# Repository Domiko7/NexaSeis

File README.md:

<p align="center">
  An open-source, collaborative seismic monitoring network built around affordable ESP32-based stations.
</p>

> [!WARNING]
> **NexaSeis is incomplete and under active development.** Expect unfinished features, breaking changes, and limited documentation. Do not rely on it for safety-critical earthquake monitoring or emergency alerts. Of the projects in `seismometer/`, only **NX-1D** is currently complete; NX-LSM6DS3 and NX-ADXL355 remain unfinished.

## Overview

NexaSeis collects waveform samples from networked seismometers, processes and stores them, and makes live station data available to other applications. This repository contains the complete stack:

- a Python ingestion and processing server;
- a Vue web interface for viewing the network and individual stations;
- firmware and KiCad design files for several ESP32-based seismometers;
- optional WebSocket, DataLink, SeedLink, and REST API services.

The server can be installed as a Python package, while its runtime behavior and station inventory remain controlled by a JSON configuration file.

## How it works

```text
ESP32 station ──UDP/TCP──> Python server ──> signal processing ──> SQLite
                                │
                                ├──> REST API / helicorders
                                ├──> WebSocket stream
                                ├──> DataLink
                                └──> SeedLink
```

Stations send fixed-size binary packets containing a timestamp, station identifiers, and five signed integer samples. The server matches each packet to a station in `src/config.json`, applies its channel sensitivity and sample rate, buffers the waveform, calculates ground-motion values, and dispatches the result to enabled outputs.

## Repository layout

| Path | Purpose |
| --- | --- |
| `src/nexaseis/` | Python server, processing pipeline, database, and services |
| `src/config.json` | Server, station, and output configuration |
| `nexaseis-web/` | Vue 3, Vuetify, and Vite web application |
| `seismometer/NX-1D/` | Complete ESP32 firmware for the ADS1256-based one-axis station |
| `seismometer/NX-LSM6DS3/` | Unfinished ESP32 firmware and KiCad hardware files for LSM6DS3 stations |
| `seismometer/NX-ADXL355/` | Unfinished ESP32/ADXL355 firmware project |
| `fdsnws/stations/` | FDSN StationXML metadata |
| `scripts/` | Development and integration helper scripts |

See the [seismometer guide](seismometer/README.md) for hardware status, NX-1D setup, and important filter limitations.

For a practical overview of the hardware, read [How to build a DIY seismometer](https://domiko.dev/blog/diy-seismometer).

## Requirements

### Server

- Python 3.11 or newer
- `obspy`
- `websockets`
- `simpledali`
- `simplemseed`
- `uvicorn`
- `fastapi[standard]`
- `numpy`

SQLite support is provided by Python's standard library and does not need a separate package.

### Web application

- Node.js 20.19+ or 22.12+
- npm

### Firmware

- PlatformIO
- an ESP32 development board
- the sensor and electronics appropriate for the selected hardware variant

## Server setup

1. Create and activate a virtual environment:

   ```bash
   python3 -m venv .venv
   source .venv/bin/activate
   ```

2. Install NexaSeis and its runtime dependencies in editable mode:

   ```bash
   python -m pip install --upgrade pip
   python -m pip install -e .
   ```

3. Edit `src/config.json`. At minimum, change `data_path` to an absolute directory writable by the server process and configure the station records you intend to receive.

4. Start the server from the repository root:

   ```bash
   ./run.sh
   ```

   The installed command and equivalent module command are:

   ```bash
   nexaseis
   python -m nexaseis
   ```

By default, a source checkout reads `src/config.json`. To keep configuration elsewhere, set `NEXASEIS_CONFIG` to its path before starting the server:

```bash
export NEXASEIS_CONFIG=/absolute/path/to/config.json
nexaseis
```

With the checked-in example configuration, the server listens on:

| Service | Default address | Purpose |
| --- | --- | --- |
| UDP ingest | `0.0.0.0:50006` | Receives station packets |
| REST API | `0.0.0.0:50010` | Station state and helicorder images |
| WebSocket | `0.0.0.0:50007` | Streams processed packets |
| DataLink | `127.0.0.1:16000` | Forwards waveform data to a DataLink server |
| TCP ingest | `0.0.0.0:50005` | Optional TCP packet input; disabled by default |
| SeedLink | `0.0.0.0:18000` | Optional SeedLink service; disabled by default |

Binding to `0.0.0.0` exposes a service on every network interface. Use a firewall and more restrictive bind addresses where appropriate.

### Station configuration

Each entry in the `stations` array identifies a station by its network, code, and location. Channels define their own calibration and sampling parameters:

```json
{
  "name": "Example Station",
  "network": "XX",
  "code": "TEST",
  "location": "00",
  "channels": {
    "EHZ": {
      "sensitivity": 5408390926,
      "sample_rate": 100
    }
  },
  "lat": 52.0,
  "lon": 21.0,
  "elevation": 100
}
```

The network, station, location, and channel values sent by the device must match this configuration. Restart the server after changing the file; configuration is loaded at startup.

### API

When the API is enabled, interactive OpenAPI documentation is available at `http://localhost:50010/docs`.

Useful endpoints include:

- `GET /` — health and server time;
- `GET /stations` — latest processed values, grouped by station;
- `GET /helicorder/{network}/{code}/{location}/{channel}?type=standard` — generated helicorder image. `type` may be `standard`, `teleseismic`, or `raw`.

Waveform packets are persisted to `nexaseis.db` beneath the configured `data_path`.

## Web application

Run the development server:

```bash
cd nexaseis-web
npm ci
npm run dev
```

Create a production build:

```bash
npm run build
```

The compiled application is written to `nexaseis-web/dist/`. Preview it locally with `npm run preview`.

## Firmware

Only `seismometer/NX-1D/` is currently considered complete. The NX-LSM6DS3 and NX-ADXL355 directories contain unfinished development work and should not be expected to build or function correctly.

Read [`seismometer/README.md`](seismometer/README.md) before configuring the firmware. It documents the required NX-1D settings and the sensor-specific limitations of its compensation and high-pass filters.

Open the NX-1D directory as a PlatformIO project. Before uploading, review its `include/settings.h` and source files for Wi-Fi credentials, station identifiers, server address, sensor pins, and calibration values.

Build the NX-1D firmware from the command line:

```bash
cd seismometer/NX-1D
pio run
```

Connect the target ESP32 and upload with:

```bash
pio run --target upload
pio device monitor
```

Never commit real Wi-Fi credentials or other secrets. Keep local values in ignored files or inject them through PlatformIO build settings.

## Development checks

The web application provides the currently configured automated checks:

```bash
cd nexaseis-web
npm run lint
npm run build
```

There is not yet an automated Python or firmware test suite. When changing the server, verify startup with a writable `data_path` and exercise the relevant input/output service.

## License

NexaSeis is licensed under the [GNU Affero General Public License v3.0](LICENSE).

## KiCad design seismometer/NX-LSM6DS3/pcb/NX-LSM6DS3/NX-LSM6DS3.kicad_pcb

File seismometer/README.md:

# NexaSeis seismometers

This directory contains the firmware and hardware work for the NexaSeis sensing devices.

See [How to build a DIY seismometer](https://domiko.dev/blog/diy-seismometer) for the accompanying hardware build guide.

> [!WARNING]
> Only **NX-1D** is currently complete. **NX-LSM6DS3** and **NX-ADXL355** are unfinished development projects and should not be expected to build or operate correctly.

## Project status

| Project | Status | Description |
| --- | --- | --- |
| [`NX-1D`](NX-1D/) | Complete | ESP32 and ADS1256 firmware for a one-axis station |
| [`NX-LSM6DS3`](NX-LSM6DS3/) | Untested | Experimental LSM6DS3 firmware (104sps not 100sps!!) |
| [`NX-ADXL355`](NX-ADXL355/) | Incomplete | Early ADXL355 firmware project |

## NX-1D setup

NX-1D is a PlatformIO project targeting an ESP32 development board. Before building or uploading it, edit [`NX-1D/include/settings.h`](NX-1D/include/settings.h) for your station and hardware.

Review at least the following settings:

- `WIFI_SSID` and `WIFI_PASSWORD` — Wi-Fi credentials;
- `CODE`, `NETWORK`, `CHANNEL`, and `LOCATION` — seismic channel identifiers, which must match the server configuration;
- `SERVER_IP`, `SERVER_PORT`, and `TRANSMISSION_PROTOCOL` — NexaSeis server connection;
- `SAMPLE_RATE`, ADC gain, input pins, and ADS1256 register values;
- ESP32 SPI, data-ready, reset, and synchronization pins;
- `ENABLE_COMPENSATION` and `ENABLE_HIGH_PASS` — optional real-time filters described below.

Do not commit real credentials or private server details to the repository.

Build and upload from the NX-1D directory:

```bash
cd seismometer/NX-1D
pio run
pio run --target upload
pio device monitor
```

## Filter limitations

The implementations controlled by `ENABLE_COMPENSATION` and `ENABLE_HIGH_PASS` are designed **only for a 4.5 Hz geophone sampled at 100 samples per second**. Do not enable them for another sensor or sample rate without calculating and validating suitable filter coefficients.

Set both options explicitly in `NX-1D/include/settings.h`:

```cpp
#define ENABLE_COMPENSATION true
#define ENABLE_HIGH_PASS true
```

Set an option to `false` when its filter is not appropriate for the connected sensor or sampling configuration.

### A note on waveform distortion

While this filter allows a $35–$50 geophone to detect low-frequency teleseismic activity, real-time Infinite Impulse Response (IIR) filters introduce phase distortion. Because different frequencies experience slight differences in group delay, wave arrivals (like P-waves and S-waves) may appear visually smoothed or stretched. For real-time event detection on low-cost hardware, this trade-off is usually well worth it.

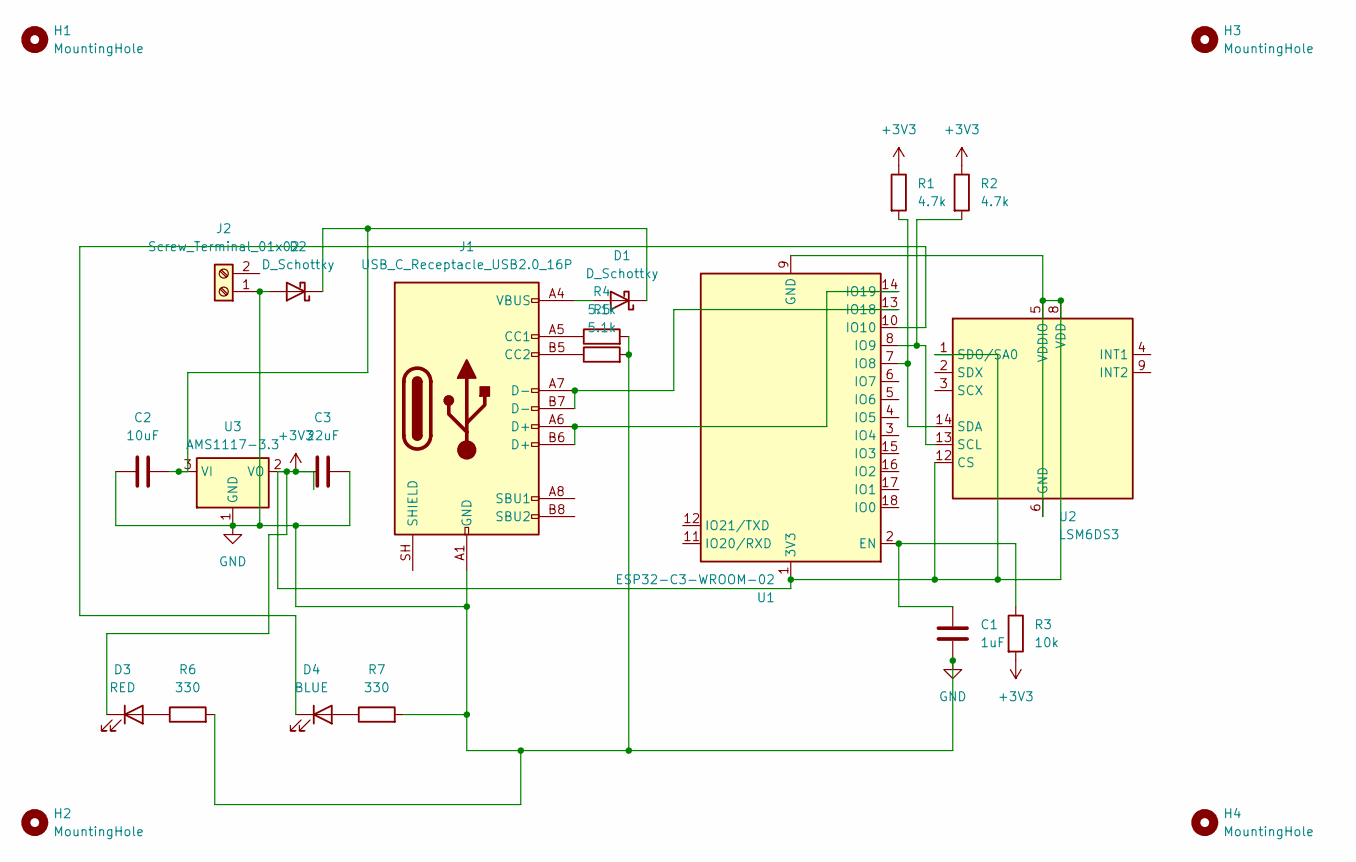
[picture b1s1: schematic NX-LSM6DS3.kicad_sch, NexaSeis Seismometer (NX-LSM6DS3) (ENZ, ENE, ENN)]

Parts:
C1: 1uF; C_0805_2012Metric
C2: 10uF; C_0805_2012Metric
C3: 22uF; C_0805_2012Metric
D1, D2: D_Schottky; D_SOD-123
D3: RED; LED_0805_2012Metric
D4: BLUE; LED_0805_2012Metric
H1, H2, H3, H4: MountingHole; MountingHole_3.2mm_M3_Pad
J1: USB_C_Receptacle_USB2.0_16P; USB_C_Receptacle_HRO_TYPE-C-31-M-12
J2: Screw_Terminal_01x02; TerminalBlock_Phoenix_MKDS-1,5-2_1x02_P5.00mm_Horizontal
R1, R2: 4.7k; R_0805_2012Metric
R3: 10k; R_0805_2012Metric
R4, R5: 5.1k; R_0805_2012Metric
R6, R7: 330; R_0805_2012Metric
U1: ESP32-C3-WROOM-02
U2: LSM6DS3; LGA-14_3x2.5mm_P0.5mm_LayoutBorder3x4y
U3: AMS1117-3.3; SOT-223-3_TabPin2

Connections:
+3V3: C3.1, D3.1 (K), R1.1, R2.1, R3.2, U1.1 (3V3), U1.9 (GND), U1.19 (GND), U2.1 (SDO/SA0), U2.5 (VDDIO), U2.6 (GND), U2.7 (GND), U2.8 (VDD), U2.12 (CS), U3.2 (VO)
GND: C1.2, C2.1, C3.2, D2.2 (A), J1.A1 (GND), J1.A12 (GND), J1.B1 (GND), J1.B12 (GND), J2.1 (Pin_1_1), R4.2, R5.2, R6.2, R7.2, U3.1 (GND)
unnamed: D1.2 (A), J1.A4 (VBUS), J1.A9 (VBUS), J1.B4 (VBUS), J1.B9 (VBUS)
unnamed: C2.2, D1.1 (K), D2.1 (K), U3.3 (VI)
unnamed: D3.2 (A), R6.1
unnamed: D4.2 (A), R7.1
unnamed: D4.1 (K), U1.10 (IO10)
unnamed: J1.A5 (CC1), R4.1
unnamed: J1.B5 (CC2), R5.1
unnamed: C1.1, R3.1, U1.2 (EN)
unnamed: R1.2, U1.7 (IO8), U2.14 (SDA)
unnamed: R2.2, U1.8 (IO9), U2.13 (SCL)
unnamed: J1.A7 (D-), J1.B7 (D-), U1.13 (IO18)
unnamed: J1.A6 (D+), J1.B6 (D+), U1.14 (IO19)

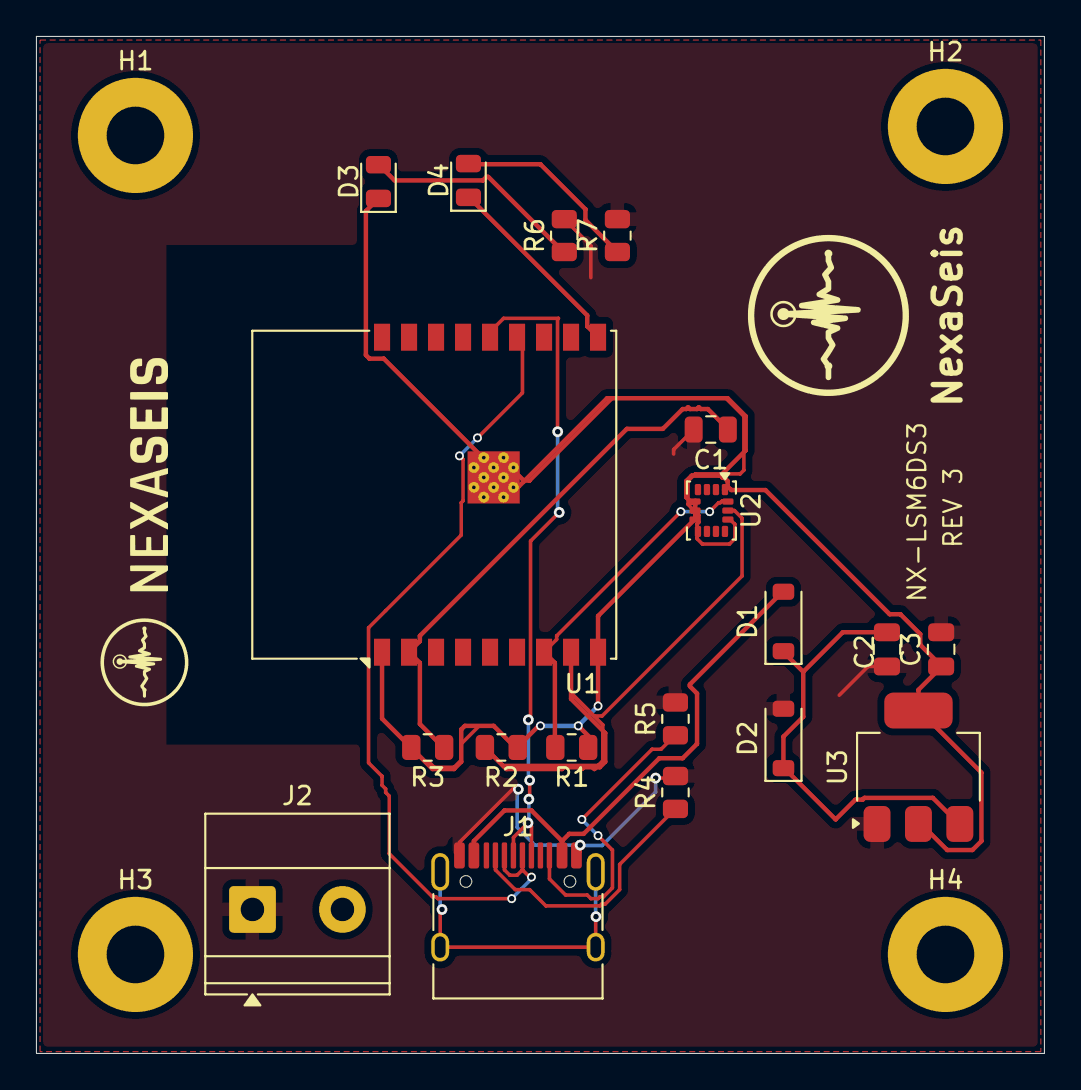
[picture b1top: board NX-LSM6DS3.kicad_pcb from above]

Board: 2 copper layers, 56.0 x 56.5 mm, 23 parts (0 on the bottom side), 14 nets.
